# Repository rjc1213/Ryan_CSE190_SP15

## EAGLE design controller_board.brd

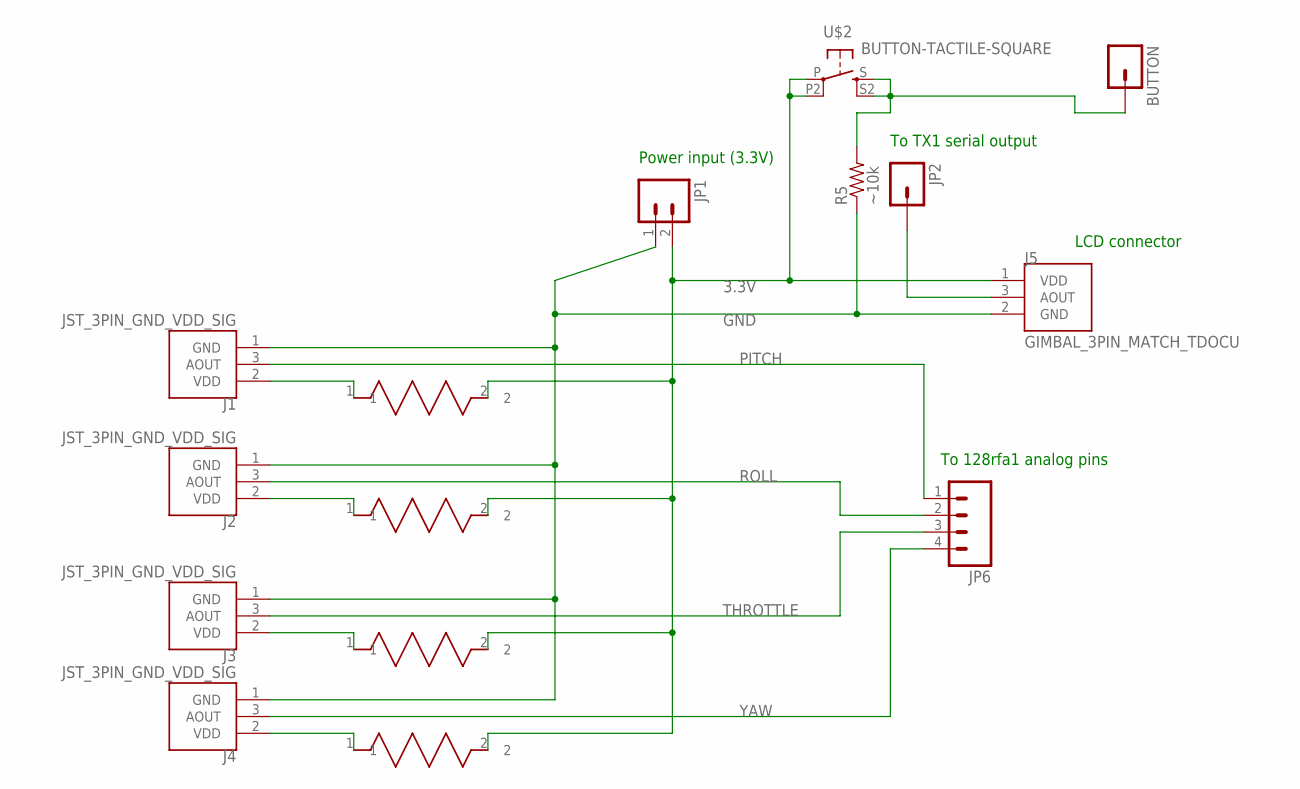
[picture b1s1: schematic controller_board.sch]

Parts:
BUTTON: M01PTH; 1X01
J1, J2, J3, J4: JST_3PIN_GND_VDD_SIG; JST-3-PTH-REVERSE
J5: GIMBAL_3PIN_MATCH_TDOCU; JST-3-PTH
JP1: M021X02_NO_SILK; 1X02_NO_SILK
JP2: M01PTH; 1X01
JP6: M04PTH; 1X04
PITCH: 2.5k; RES_CRF12
R5: ~10k; AXIAL-0.4
ROLL: 2.5k; RES_CRF12
THROTTLE: 2.5k; RES_CRF12
U$2: BUTTON-TACTILE-SQUARE; BUTTON-TACTILE-SQUARE-ADAFRUIT1010
YAW: 2.5k; RES_CRF12

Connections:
3.3V: J5.1 (VDD), JP1.2, PITCH.2, ROLL.2, THROTTLE.2, U$2.P, U$2.P2 (P1), YAW.2
GND: J1.1 (GND), J2.1 (GND), J3.1 (GND), J4.1 (GND), J5.2 (GND), JP1.1, R5.P$1 (1)
unnamed: J1.2 (VDD), PITCH.1
unnamed: J2.2 (VDD), ROLL.1
unnamed: J3.2 (VDD), THROTTLE.1
unnamed: J4.2 (VDD), YAW.1
unnamed: BUTTON.1, R5.P$2 (2), U$2.S, U$2.S2 (S1)
unnamed: J5.3 (AOUT), JP2.1
PITCH: J1.3 (AOUT), JP6.1
ROLL: J2.3 (AOUT), JP6.2
THROTTLE: J3.3 (AOUT), JP6.3
YAW: J4.3 (AOUT), JP6.4

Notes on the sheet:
To 128rfa1 analog pins
LCD connector
Power input (3.3V)
To TX1 serial output

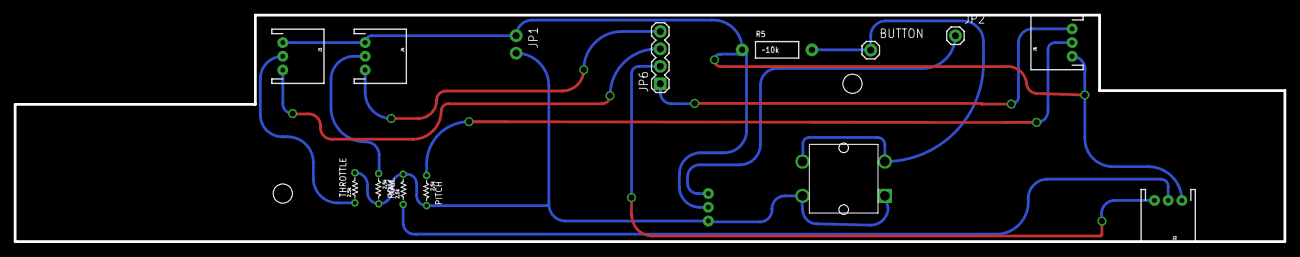
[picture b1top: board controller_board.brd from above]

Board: 2 copper layers, 185.0 x 33.0 mm, 16 parts (1 on the bottom side), 12 nets.

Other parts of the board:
U$1: CONNECTOR_BOARD_OUTLINE

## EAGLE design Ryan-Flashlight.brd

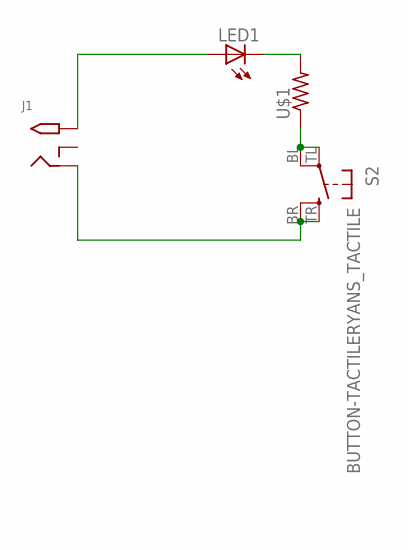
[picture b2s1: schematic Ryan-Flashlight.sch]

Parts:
J1: 2.1MMJACKTHM; PJ-102A
LED1: LED5MM
S2: BUTTON-TACTILERYANS_TACTILE; TACTILE_1
U$1: RESISTORTH-1/4W-CARBON; RESAD1160W55L680D260_HS

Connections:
unnamed: J1.TIP, LED1.A
unnamed: LED1.K (C), U$1.2
unnamed: S2.BL (P1), S2.TL, U$1.1
unnamed: J1.RING, S2.BR (S1), S2.TR (S)

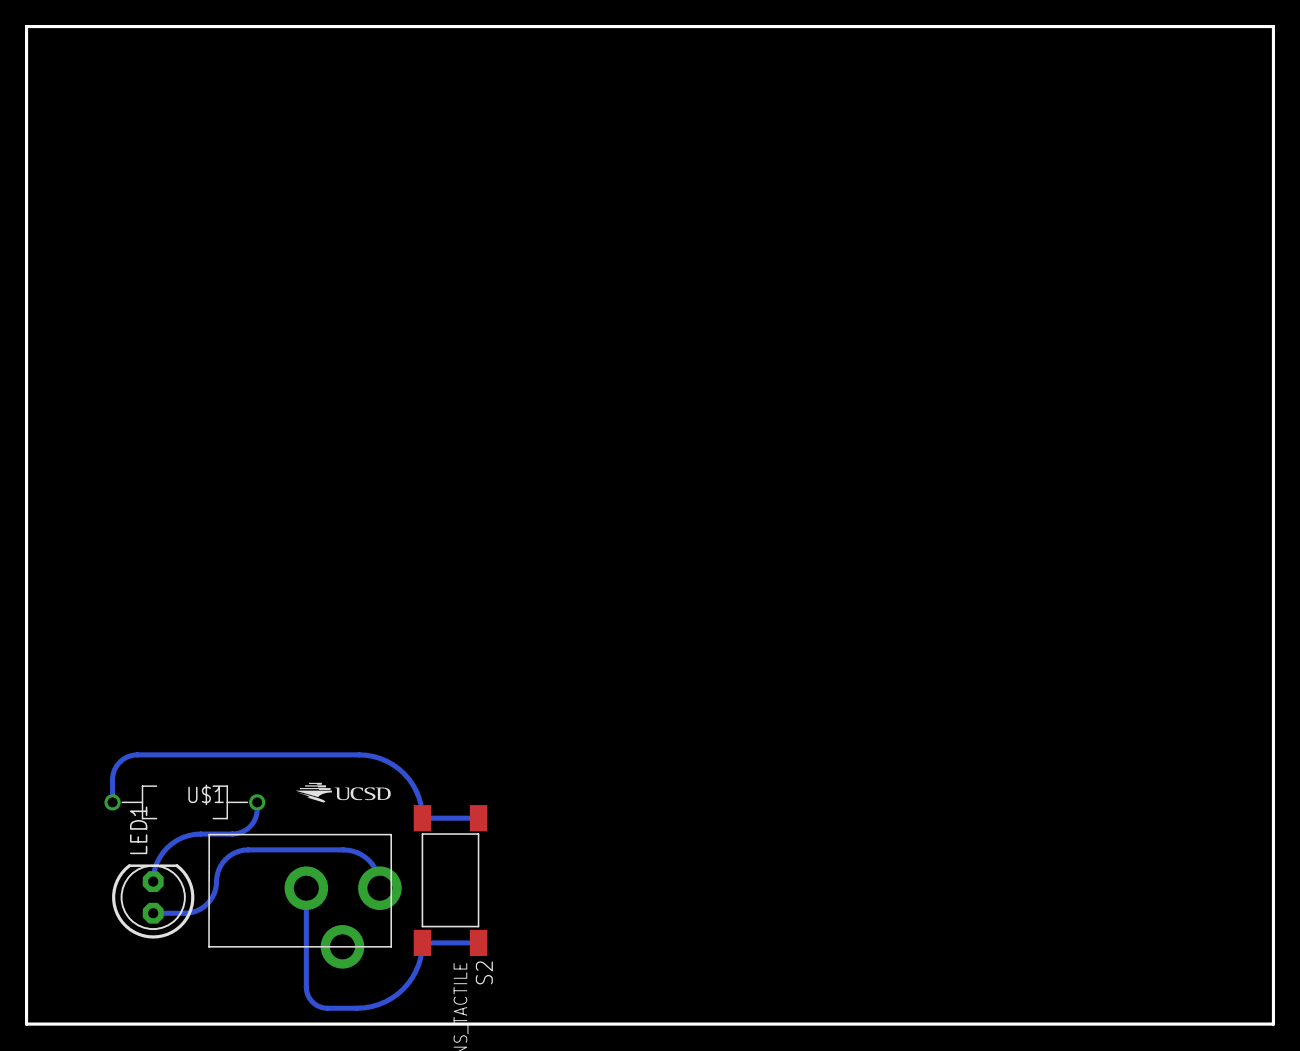
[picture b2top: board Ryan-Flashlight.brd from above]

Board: 2 copper layers, 100.0 x 80.0 mm, 5 parts (0 on the bottom side), 4 nets.

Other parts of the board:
U$2: UCSD_LOGO

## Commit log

2015-04-12 This is my first commit, I hope I did it corectly This is my Lab 2, sorry for turning it in late, I had a really rough time with GitHub, took me forever to figure out. I did turn in lab 3 early, mayb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
2015-04-18 This is my lab 4 commit

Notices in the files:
parts and their libraries:
SparkFun-Connectors: Licensing: Creative Commons ShareAlike 4.0 International - https://creativecommons.org/licenses/by-sa/4.0
